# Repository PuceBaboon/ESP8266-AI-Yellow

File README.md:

# ESP8266-AI-Yellow
Repository of ESP8266 demo programs specific to the AI-Thinker "Yellow Development Board"

The hardware information related to these demo programs is available at <https://esp8266hints.wordpress.com/2016/11/15/yellow-doorbelldash-project/>.  Note that these programs will work on an unmodified "Yellow Development Board", but obviously the auto power-off will not function. The Eagle board files for the auto-latching switch are available in the `Eagle` sub-directory.  The board itself is also available from OSH Park's shared projects page <https://oshpark.com/shared_projects/iFWjTLa5>

## Demo Programs

There are currently two different demos in this repository.  Both use the same basic hardware, the AI-Thinker produced "Yellow Development Board", which has been widely available on Ebay and Aliexpress for almost two years now.

The first demo is named:- `Initial_Power+LEDs.ino`

`Initial_Power+LEDs.ino` will work, even without a valid access-point and will quite happily flash the lights on your "Yellow" board and update the serial console every couple of seconds withe the ADC reading from the on-board LDR.  If you have a latching MOSFET power switch attached (GPIO-16 is the default drive pin), then it will switch itself off after three minutes of operation.  If you don't have the latching power-switch circuitry, it will quite happily continue running until it has exhausted the batteries.

Note that even this simple version has the Arduino OTA (Over The Air) bootloader enabled, so you should only need to flash the device via the serial connections once.  After that initial serial flash cycle you can flash via WiFi (much faster!).  Under Platformio (the build environment I currently prefer and recommend), you simply need to add one line to the bottom of your platformio.ini file, reading `upload_port = 192.168.172.236`, where the IP address is the one for your specific device on your local network.

The second demo is named:- `MQTT+LEDs.ino`

`MQTT+LEDs.ino`, as the name suggests, **must** have an accessible local network to function.  **!!IMPORTANT!!** You **must** update the settings for IP addresses and Access-Point SSID and password in the `user_config.h` file before attempting to run this demo.  The `user_config.h` file also has a default setting for an MQTT broker (server) of "broker.hivemq.com".  This is a publicly accessible MQTT service running out of Landshut, near Munich in Germany.  HiveMQ provide tutorials and support for MQTT, as well as providing this free service to allow users like you and me to experiment with the system.  Please be nice if you use this service and keep your publications down to a reasonable number per hour (also remember that anyone, anywhere can read and potentially overwrite your topics, so be circumspect in what you publish.

The web dashboard to see the data being handled by the HiveMQ server is available at <http://www.mqtt-dashboard.com/>.  Note that the server is handling many millions of requests per day and it's not unusual to see more than 1,000 active clients at any one time, so it can be quite difficult to spot your particular data popping up on the dashboard.  A better option is probably to install a version of the Mosquitto broker on your local machine.

The Mosquitto package comes with two command-line utilities, mosquitto_pub and mosquitto_sub, which allow you to publish or subscribe to topics from your desktop without needing to run the actual server process (for example, `mosquitto_sub -h broker.hivemq.com -t Yellow/LDR` will subscribe to the "Yellow/LDR" topic from the HiveMQ public server.  You will see your own data as it is published, as well as anyone else's data being published to that same topic).

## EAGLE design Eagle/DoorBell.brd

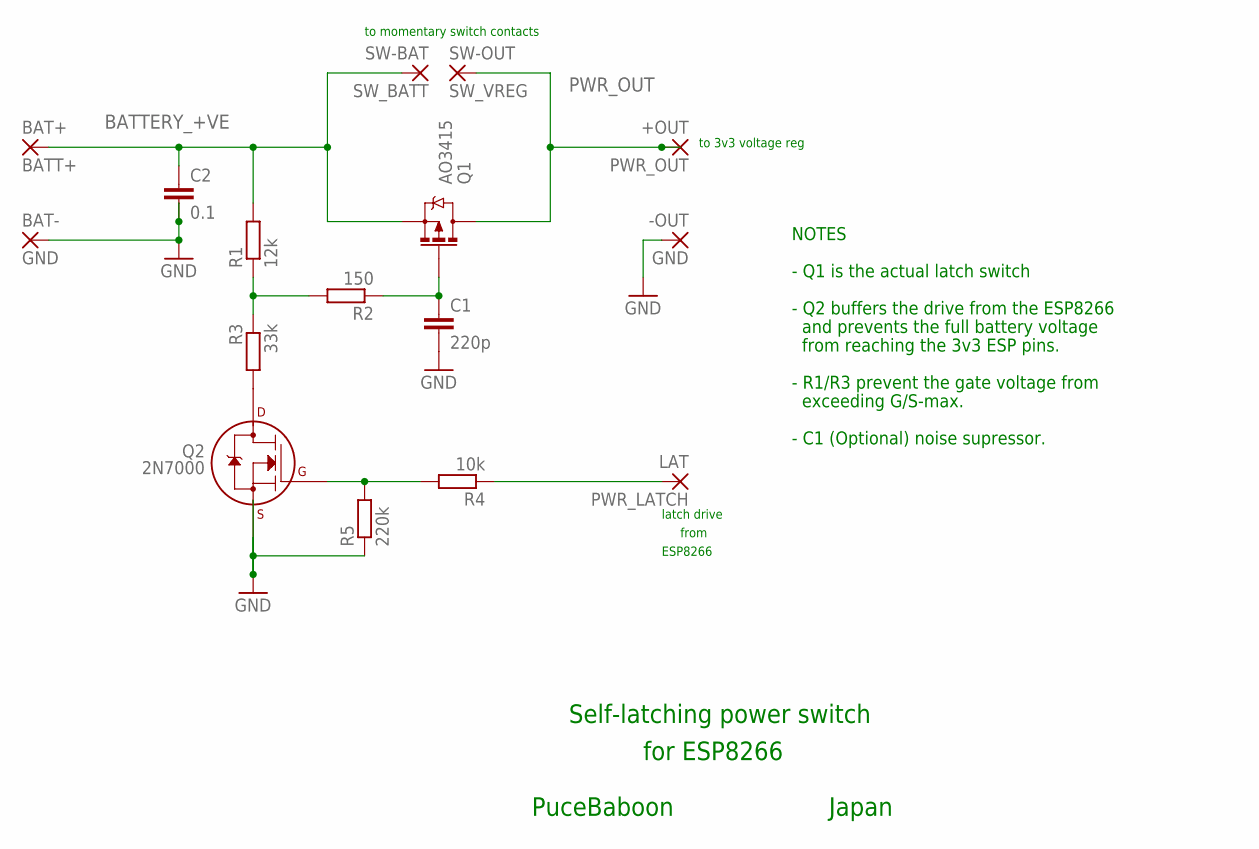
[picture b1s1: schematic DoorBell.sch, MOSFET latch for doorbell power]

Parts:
+OUT: PWR_OUT; 2,54/0,9
-OUT: GND; 2,54/0,9
BAT+: BATT+; 2,54/0,9
BAT-: GND; 2,54/0,9
C1: 220p; C025-025X050
C2: 0.1; C025-025X050
LAT: PWR_LATCH; 2,54/0,9
Q1: AO3415; SOT23-3
Q2: 2N7000; TO-92
R1: 12k; 0204/7
R2: 150; 0204/7
R3: 33k; 0204/7
R4: 10k; 0204/7
R5: 220k; 0204/7
SW-BAT: SW_BATT; 2,54/0,9
SW-OUT: SW_VREG; 2,54/0,9

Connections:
BATTERY_+VE: BAT+.1, C2.1, Q1.2 (S), R1.2, SW-BAT.1
GND: -OUT.1, BAT-.1, C1.2, C2.2, Q2.1 (S), R5.1
unnamed: R1.1, R2.2, R3.1
unnamed: C1.1, Q1.1 (G), R2.1
unnamed: Q2.3 (D), R3.2
unnamed: Q2.2 (G), R4.2, R5.2
PWR_LATCH: LAT.1, R4.1
PWR_OUT: +OUT.1, Q1.3 (D), SW-OUT.1

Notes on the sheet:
to momentary switch contacts
latch drive
to 3v3 voltage reg
NOTES
- Q1 is the actual latch switch
- Q2 buffers the drive from the ESP8266
and prevents the full battery voltage
from reaching the 3v3 ESP pins.
- R1/R3 prevent the gate voltage from
exceeding G/S-max.
Self-latching power switch
for ESP8266
PuceBaboon
Japan
- C1 (Optional) noise supressor.
from
ESP8266

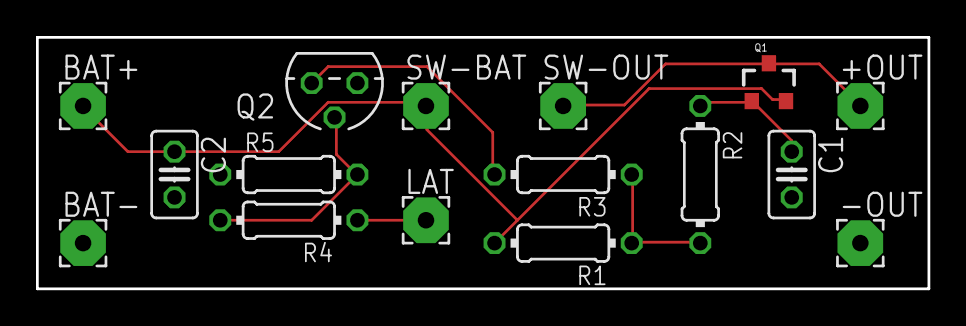
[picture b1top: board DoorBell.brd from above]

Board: 2 copper layers, 49.5 x 14.0 mm, 16 parts (0 on the bottom side), 8 nets.

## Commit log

2016-11-14 Update README.md
    Minor addition, just to get started.
2016-11-14 Create LICENCE
2016-11-17 Initial upload of files.
2016-11-17 Replaced MQTT infor with generic "change this" entries.
2016-11-17 Added info on first demo file.
    Details specific to Initial_Power+LEDs.ino.
2016-11-17 Typoos, typus, typohs. Y'know what I mean!
2016-11-17 Update README.md
    Added link to hardware pages.
2016-11-19 Added Eagle directory for auto-latch power switch board files.
2016-11-19 Update README.md
    Added link to board files and board order page.
2016-11-19 Minor typo fix.
2016-11-19 Added a header for "Demo Programmes".
2016-11-20 Update README.md
    Added board image
2016-11-20 Update README.md
    Updated board image with smaller version
2016-11-20 Update README.md
    Added header image of "Yellow" board.
2016-11-20 Update README.md
    Corrected anudder spuling mestike
2016-11-21 Mainly updates to the MQTT section to enable sensible defaults for the new MQTT+LEDs demo. Updated the pre-set IP addresses with some anonymous, fictional numbers and comments to change before use.
2016-11-21 Import of MQTT+LEDs.ino from PlatformIO environment.
2016-11-21 Added initial spiel on MQTT version.
2016-11-21 Fixed link. Broke down into additional paras.
2016-11-21 Updated Mosquitto section to make clear that the user doesn't need to run the server to use _pub and _sub utilities.
2016-11-24 Deleted commented-out analog-read call.
2016-11-30 Changed the sendmqttMsg() call again to cast only the TOPIC argument (it's the only one causing a warning message).
2016-11-30 Some very minor changes to the debug output print routines around the power latch on/off routines to bring this version in line with the MQTT version.
2016-12-01 Changed MQTT_CLIENT_ID format to "YDB_%08X" to give the full, 32-bit unique ID number (returned by getChipId()) as the MQTT client ID for this specific ESP8266 (and "YDB" for Yellow Development Board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
2016-12-02 Minor changes to MQTT comments and update of CVS revision lines in header.
2016-12-06 Updated TOPIC names to indicate use.
2016-12-06 Ran through indent to clean up recent changes.
2016-12-06 Cleaned up ordering and comments in loop() to make operation as obvious as possible.
